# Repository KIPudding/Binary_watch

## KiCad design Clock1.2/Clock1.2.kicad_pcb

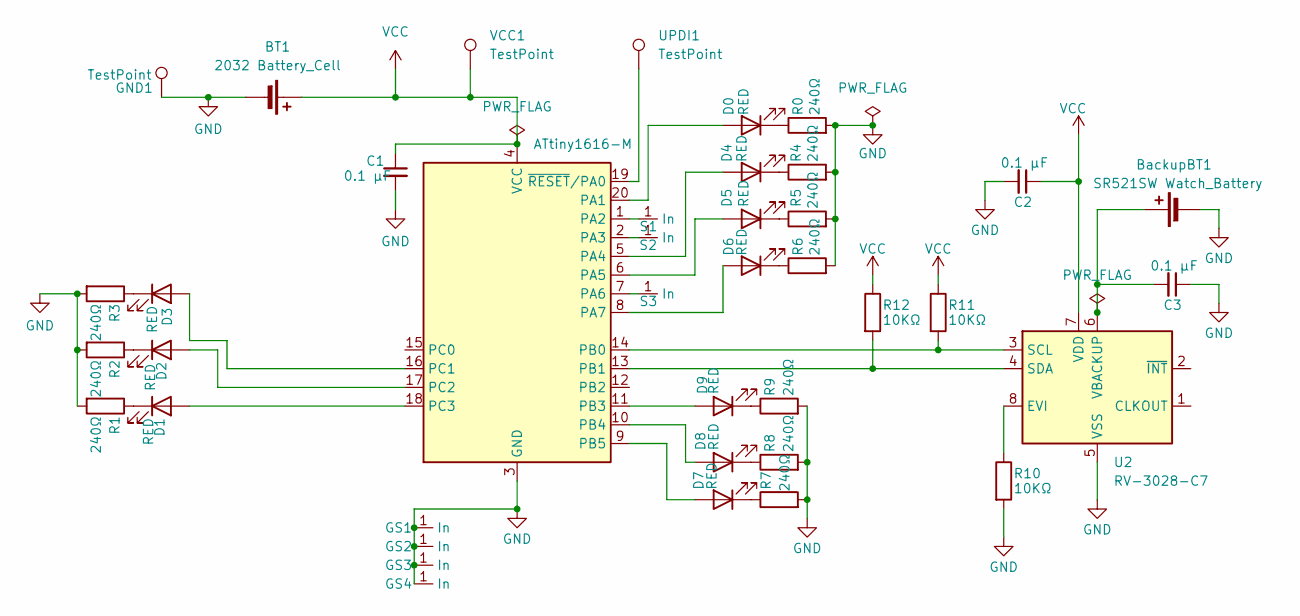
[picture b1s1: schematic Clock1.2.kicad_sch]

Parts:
BT1: 2032 Battery_Cell; MY-2032-11; MFR.Part # MY-2032-11; JLCPCB Part # C2988622
BackupBT1: SR521SW Watch_Battery; MY-521-01; MFR.Part # MY-521-01
C1, C2, C3: 0.1 µF; C_0201_0603Metric; MFR.Part # CL03A104KQ3NNNC; JLCPCB Part # C49062
D0, D1, D2, D3, D4, D5, D6, D7, D8, D9: RED; MiNiPLCC-2; MFR.Part # 5988C10107F; JLCPCB Part # C5355454
GND1: TestPoint; SolderPoints
GS1, GS2, GS3, GS4: SolderPoints
R0, R1, R2, R3, R4, R5, R6, R7, R8, R9: 240Ω; R_0603_1608Metric; MFR.Part # RC0603FR-07240RL; JLCPCB Part # C25087
R10: 10KΩ; R_0201_0603Metric; MFR.Part # RC0201FR-0710KL; JLCPCB Part # C25087
R11, R12: 10KΩ; R_0603_1608Metric; MFR.Part # RC0603FR-0710KL; JLCPCB Part # C25087
S1, S2, S3: SolderPoints
U1: ATtiny1616-M; VQFN-20-1EP_3x3mm_P0.4mm_EP1.7x1.7mm; MFR.Part # ATTINY1616-MNR; JLCPCB Part # C507118
U2: RV-3028-C7; MicroCrystal_C7_SON-8_1.5x3.2mm_P0.9mm; MFR.Part # RV-3028-C7-32.768kHz-1ppm-TA-QC
UPDI1: TestPoint; SolderPoints
VCC1: TestPoint; SolderPoints

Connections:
GND: BT1.2 (-), BackupBT1.2 (-), C1.2, C2.2, C3.1, GND1.1, GS1.1 (In), GS2.1 (In), GS3.1 (In), GS4.1 (In), R0.2, R1.2, R2.2, R3.2, R4.2, R5.2, R6.2, R7.2, R8.2, R9.2, R10.2, U1.3 (GND), U1.21 (GND), U2.5 (VSS); also elsewhere on the board
unnamed: BackupBT1.1 (+), C3.2, U2.6 (VBACKUP)
unnamed: D0.2 (A), U1.20 (PA1)
unnamed: D0.1 (K), R0.1
unnamed: D1.2 (A), U1.18 (PC3)
unnamed: D1.1 (K), R1.1
unnamed: D2.2 (A), U1.17 (PC2)
unnamed: D2.1 (K), R2.1
unnamed: D3.2 (A), U1.16 (PC1)
unnamed: D3.1 (K), R3.1
unnamed: D4.2 (A), U1.5 (PA4)
unnamed: D4.1 (K), R4.1
unnamed: D5.2 (A), U1.6 (PA5)
unnamed: D5.1 (K), R5.1
unnamed: D6.2 (A), U1.8 (PA7)
unnamed: D6.1 (K), R6.1
unnamed: D7.2 (A), U1.9 (PB5)
unnamed: D7.1 (K), R7.1
unnamed: D8.2 (A), U1.10 (PB4)
unnamed: D8.1 (K), R8.1
unnamed: D9.2 (A), U1.11 (PB3)
unnamed: D9.1 (K), R9.1
unnamed: S1.1 (In), U1.1 (PA2)
unnamed: S2.1 (In), U1.2 (PA3)
unnamed: S3.1 (In), U1.7 (PA6)
unnamed: R11.2, U1.14 (PB0), U2.3 (SCL)
unnamed: R12.2, U1.13 (PB1), U2.4 (SDA)
unnamed 27: U1.19 (~RESET/PA0), UPDI1.1; also elsewhere on the board
unnamed: R10.1, U2.8 (EVI)
VCC: BT1.1 (+), C1.1, C2.1, R11.1, R12.1, U1.4 (VCC), U2.7 (VDD), VCC1.1; also elsewhere on the board

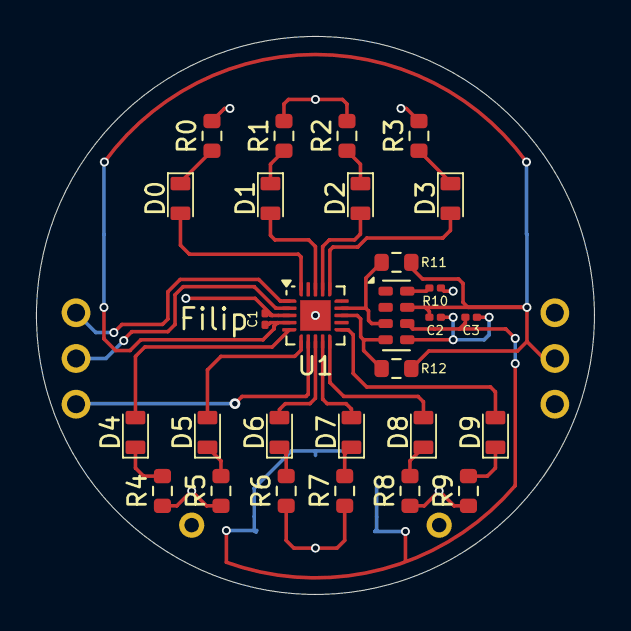
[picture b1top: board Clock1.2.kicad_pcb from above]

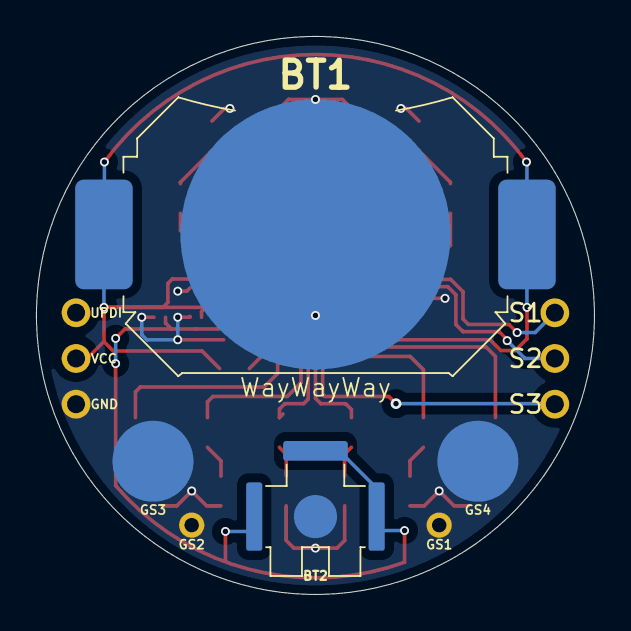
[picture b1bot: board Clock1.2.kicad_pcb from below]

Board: 2 copper layers, 31.0 x 31.0 mm, 40 parts (12 on the bottom side), 30 nets.

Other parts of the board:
GND: TestPoint; SolderPoints
UPDI: TestPoint; SolderPoints
VCC: TestPoint; SolderPoints

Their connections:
GND: GND.1; also elsewhere on the board
unnamed 27: UPDI.1; also elsewhere on the board
VCC: VCC.1; also elsewhere on the board

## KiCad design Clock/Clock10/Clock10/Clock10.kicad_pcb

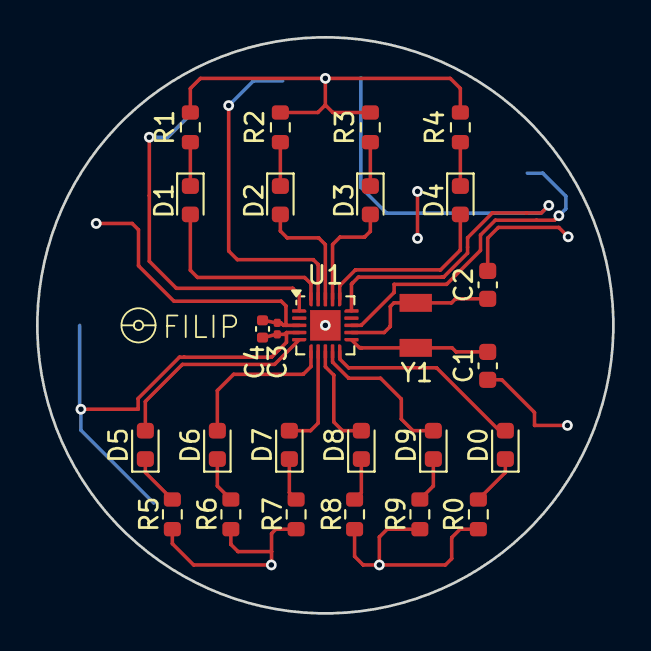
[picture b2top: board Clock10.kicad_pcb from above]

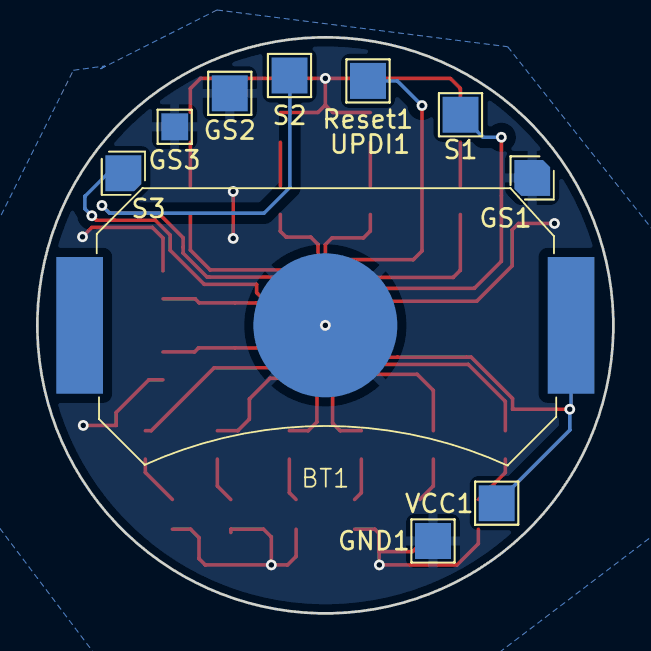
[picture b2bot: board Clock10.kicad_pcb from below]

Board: 2 copper layers, 32.0 x 32.0 mm, 36 parts (10 on the bottom side), 25 nets.

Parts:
BT1: 2450 Battery_Cell; MY-2450-03
C1, C2: 15pf; C_0603_1608Metric
C3: 0.1 µF; C_0201_0603Metric
C4: 10 µF; C_0402_1005Metric
D0, D1, D2, D3, D4, D5, D6, D7, D8, D9: RED; LED_0603_1608Metric
GND1: TestPoint; TestPoint_Pad_2.0x2.0mm
GS1, GS2: TestPoint_Pad_2.0x2.0mm
GS3: TestPoint_Pad_1.5x1.5mm
R0, R1, R2, R3, R4, R5, R6, R7, R8, R9: 50Ω; R_0603_1608Metric
Reset1: TestPoint; TestPoint_Pad_2.0x2.0mm
S1, S2, S3: TestPoint_Pad_2.0x2.0mm
U1: ATtiny1616-M; VQFN-20-1EP_3x3mm_P0.4mm_EP1.7x1.7mm
VCC1: TestPoint; TestPoint_Pad_2.0x2.0mm
Y1: Crystal; FC31M2-32.768-NTLNNDTL

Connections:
GND: BT1.2 (-), C1.2, C2.2, C3.2, C4.2, GND1.1, GS1.1 (In), GS2.1 (In), GS3.1 (In), R0.2, R1.2, R2.2, R3.2, R4.2, R5.2, R6.2, R7.2, R8.2, R9.2, U1.3 (GND), U1.21 (GND)
unnamed: D0.2 (A), U1.10 (PB4)
unnamed: D0.1 (K), R0.1
unnamed: D1.2 (A), U1.20 (PA1)
unnamed: D1.1 (K), R1.1
unnamed: D2.2 (A), U1.18 (PC3)
unnamed: D2.1 (K), R2.1
unnamed: D3.2 (A), U1.17 (PC2)
unnamed: D3.1 (K), R3.1
unnamed: D4.2 (A), U1.16 (PC1)
unnamed: D4.1 (K), R4.1
unnamed: D5.2 (A), U1.5 (PA4)
unnamed: D5.1 (K), R5.1
unnamed: D6.2 (A), U1.6 (PA5)
unnamed: D6.1 (K), R6.1
unnamed: D7.2 (A), U1.7 (PA6)
unnamed: D7.1 (K), R7.1
unnamed: D8.2 (A), U1.8 (PA7)
unnamed: D8.1 (K), R8.1
unnamed: D9.2 (A), U1.9 (PB5)
unnamed: D9.1 (K), R9.1
unnamed: C2.1, U1.12 (PB2), Y1.1
unnamed: C1.1, U1.11 (PB3), Y1.2
unnamed: Reset1.1, U1.19 (~RESET/PA0)
VCC: BT1.1 (+), C3.1, C4.1, U1.4 (VCC), VCC1.1

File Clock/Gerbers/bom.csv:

Designator,Footprint,Quantity,Value,LCSC Part #
BT1,MY-2450-03,1,2450 Battery_Cell,C2988622
"C1, C2",0603,2,15pf, C1644
C3,0201,1,0.1 µF,C49062
C4,0402,1,10 µF, C15525
"D0, D1, D2, D3, D4, D5, D6, D7, D8, D9",0603,10,RED,C5355430
"GND1, RESET1, VCC1",TestPoint_Pad_2.0x2.0mm,3,TestPoint,
"GS1, GS2, S1, S2, S3",TestPoint_Pad_2.0x2.0mm,5,~,
GS3,TestPoint_Pad_1.5x1.5mm,1,~,
"R0, R1, R2, R3, R4, R5, R6, R7, R8, R9",0603,10,50Ω,C23197
U1,VQFN-20-1EP_3x3mm_P0.4mm_EP1.7x1.7mm,1,ATtiny1616-M, C507118
Y1,FC31M2-32.768-NTLNNDTL,1,Crystal, C5120559
